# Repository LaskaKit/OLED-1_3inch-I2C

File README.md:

# LaskaKit OLED 1.3" Display with uSUP 

We have a lot of modules and boards what support our uSUP connector (compatible with Qiik and Stemma). You can measure temperature/humidity with [SHT40](https://www.laskakit.cz/laskakit-sht40-senzor-teploty-a-vlhkosti-vzduchu/), pressure with [BME280](https://www.laskakit.cz/arduino-senzor-tlaku--teploty-a-vlhkosti-bme280/), CO2 with [SCD41](https://www.laskakit.cz/laskakit-scd41-senzor-co2--teploty-a-vlhkosti-vzduchu/) and now we would like to introduce 1.3" OLED with two uSUP connectors and also includes footprint for 2.54mm header connector. 

The range of input power supply is huge - from 3.3 to 5V. The I2C bus includes 10k pull-up rezistors what are conencted. 
Do you need two OLED? Ok, use solder bridge where you can choose the I2C address - 0x3C or 0x3D. 
Resolution: 128x64
Driver: SH1106

https://www.laskakit.cz/laskakit-oled-displej-128x64-1-3--i2c/

Library: https://github.com/adafruit/Adafruit_SH110X/

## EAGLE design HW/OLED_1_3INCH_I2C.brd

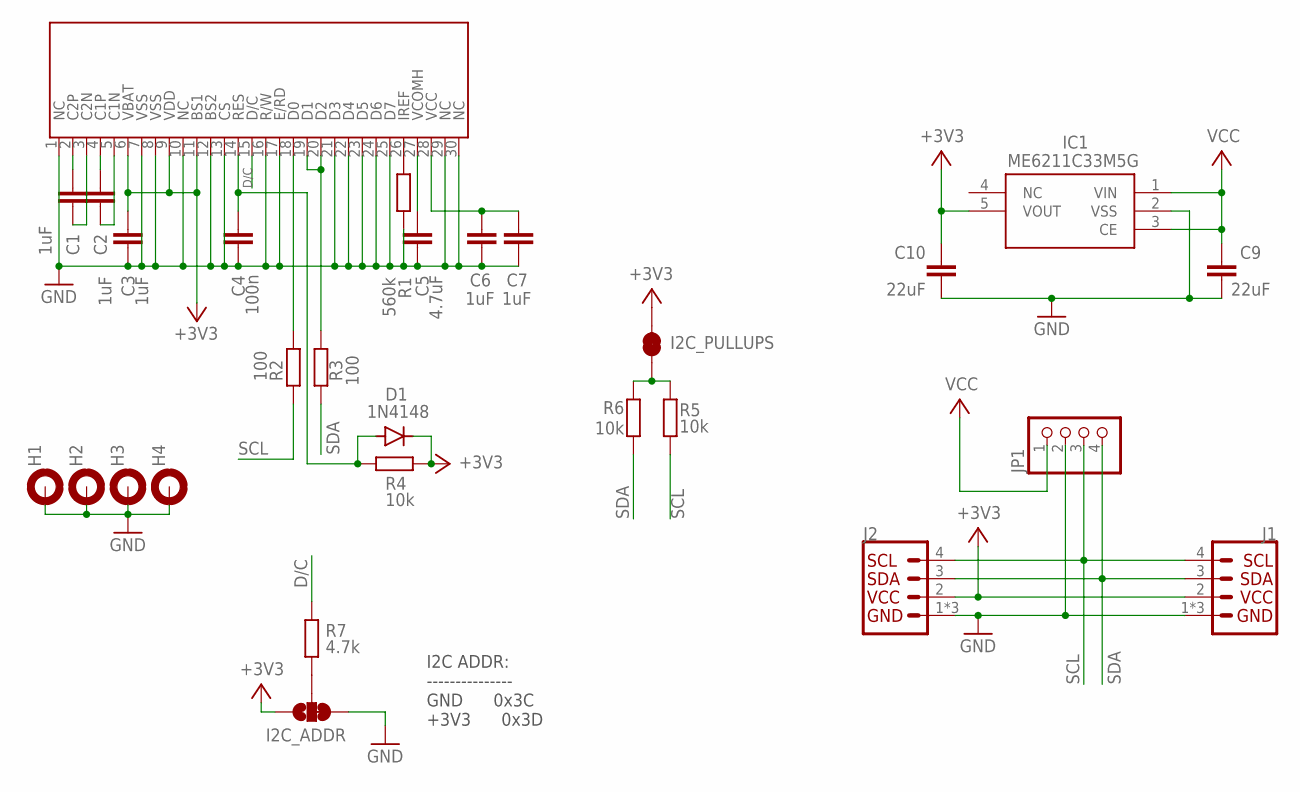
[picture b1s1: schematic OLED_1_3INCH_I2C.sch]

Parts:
C1, C2, C3, C6, C7: 1uF; C0603
C4: 100n; C0603
C5: 4.7uF; C0603
C9, C10: 22uF; C0603
D1: 1N4148; SOD323-R
DISPLAY1: OLED_1_3INCH; GME12864_1_3INCH
H1, H2, H3, H4: MOUNT-PAD-ROUND2.5; 2,5-PAD
I2C_ADDR: JUMPER-SMT_3_1-NC_TRACE_NO-SILK; SMT-JUMPER_3_1-NC_TRACE_NO-SILK
I2C_PULLUPS: JUMPER-SMT_2_NC_TRACE_SILK; SMT-JUMPER_2_NC_TRACE_SILK
IC1: ME6211C33M5G; SOT23-5
J1, J2: USUP_CONNECTOR_HOR; 1X04_1MM_RA
JP1: PINHD-1X4; 1X04
R1: 560k; R0603
R2, R3: 100; R0603
R4, R5, R6: 10k; R0603
R7: 4.7k; R0603

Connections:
+3V3: C3.1, C10.1, D1.C, DISPLAY1.6 (VBAT), DISPLAY1.9 (VDD), DISPLAY1.11 (BS1), I2C_ADDR.1, I2C_PULLUPS.2, IC1.5 (VOUT), J1.2 (VCC), J2.2 (VCC), R4.1
D/C: DISPLAY1.15 (D/C), R7.1
GND: C3.2, C4.2, C5.2, C6.2, C7.2, C9.2, C10.2, DISPLAY1.1 (NC), DISPLAY1.7 (VSS), DISPLAY1.8 (VSS), DISPLAY1.10 (NC), DISPLAY1.12 (BS2), DISPLAY1.13 (CS), DISPLAY1.16 (R/W), DISPLAY1.17 (E/RD), DISPLAY1.21 (D3), DISPLAY1.22 (D4), DISPLAY1.23 (D5), DISPLAY1.24 (D6), DISPLAY1.25 (D7), DISPLAY1.29 (NC), DISPLAY1.30 (NC), H1.1, H2.1, H3.1, H4.1, I2C_ADDR.3, IC1.2 (VSS), J1.1 (GND), J1.NC1 (GND), J1.NC2 (GND), J2.1 (GND), J2.NC1 (GND), J2.NC2 (GND), JP1.2, R1.1
unnamed: C1.2, DISPLAY1.3 (C2N)
unnamed: C2.2, DISPLAY1.5 (C1N)
unnamed: C2.1, DISPLAY1.4 (C1P)
unnamed: C1.1, DISPLAY1.2 (C2P)
unnamed: I2C_ADDR.2, R7.2
unnamed: C4.1, D1.A, DISPLAY1.14 (RES), R4.2
unnamed: C5.1, DISPLAY1.27 (VCOMH)
unnamed: C6.1, C7.1, DISPLAY1.28 (VCC)
unnamed: DISPLAY1.26 (IREF), R1.2
unnamed: DISPLAY1.19 (D1), DISPLAY1.20 (D2), R3.2
unnamed: DISPLAY1.18 (D0), R2.2
unnamed: I2C_PULLUPS.1, R5.1, R6.1
SCL: J1.4 (SCL), J2.4 (SCL), JP1.3, R2.1, R5.2
SDA: J1.3 (SDA), J2.3 (SDA), JP1.4, R3.1, R6.2
VCC: C9.1, IC1.1 (VIN), IC1.3 (CE), JP1.1

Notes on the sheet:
I2C ADDR: --------------- GND 0x3C +3V3 0x3D

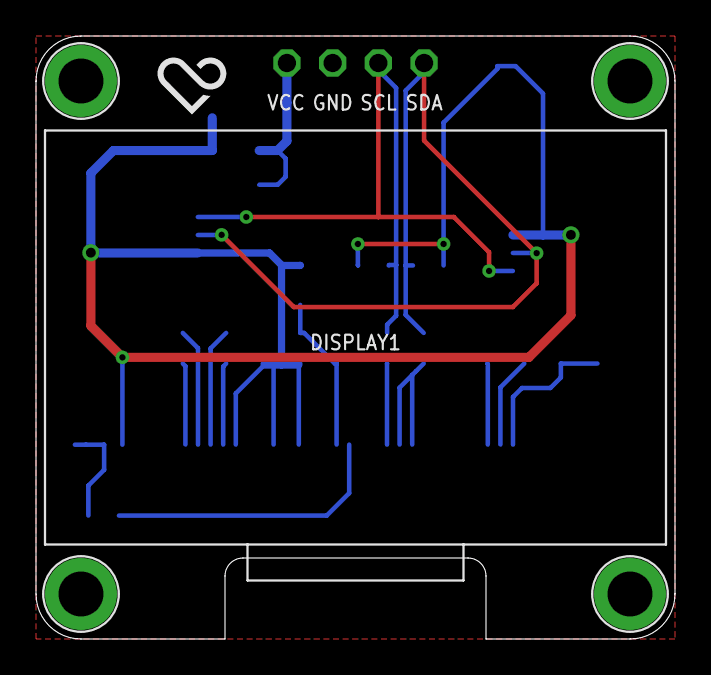
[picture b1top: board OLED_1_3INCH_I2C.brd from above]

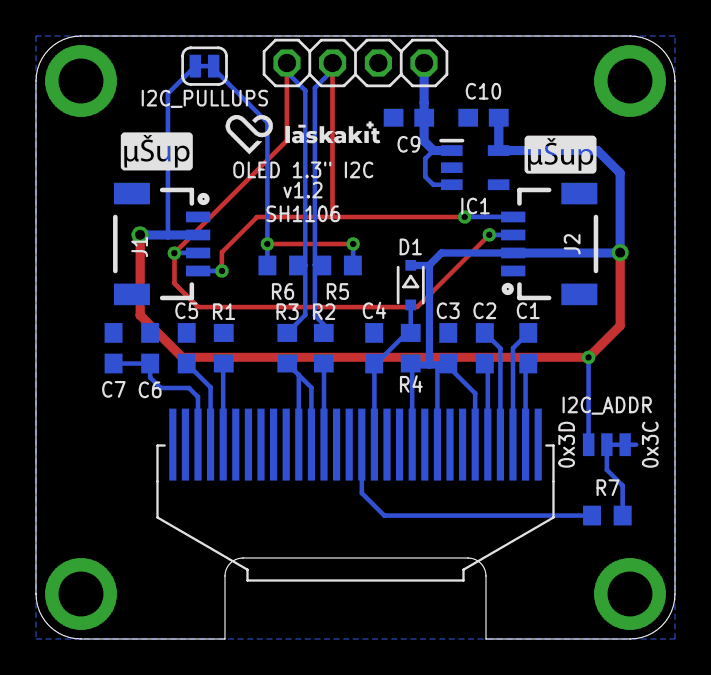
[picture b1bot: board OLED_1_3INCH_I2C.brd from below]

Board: 2 copper layers, 35.5 x 33.5 mm, 32 parts (26 on the bottom side), 18 nets.

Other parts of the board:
U$1, U$2: USUP_4MM_SILKSCREEN
U$3: LASKAKIT_HEART_4MM
U$4: LASKKIT_10MM_SILKSCREEN

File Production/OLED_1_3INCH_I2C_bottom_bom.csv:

Comment,Designator,Footprint,LCSC Part #
1N4148,D1,SOD323-R,
1uF,C1 C2 C3 C6 C7,C0603,
4.7k,R7,R0603,
4.7uF,C5,C0603,
10k,R4 R5 R6,R0603,
22uF,C9 C10,C0603,
100,R2 R3,R0603,
100n,C4,C0603,
560k,R1,R0603,
ME6211C33M5G,IC1,SOT23-5,
4p,J1 J2,4p,C145956

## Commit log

2023-02-18 fixing mistakes and update folders
2023-04-24 new version
2025-01-30 delete

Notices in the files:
parts and their libraries:
LaskaKit-Jumpers: Licensing: Creative Commons ShareAlike 4.0 International - https://creativecommons.org/licenses/by-sa/4.0
